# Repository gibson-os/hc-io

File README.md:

### Commands
| Number | Description           |
|--------|-----------------------|
| 128    | Set ports             |
| 129    | Add direct connect    |
| 130    | Set direct connect    |
| 131    | Delete direct connect |
| 132    | Reset direct connect  |
| 133    | Get direct connect    |
| 134    | Defrag direct connect |
| 135    | Status in EEPROM      |
| 136    | Direct connect status |

Basic commands: [Module readme](src/hc-module/README.md)

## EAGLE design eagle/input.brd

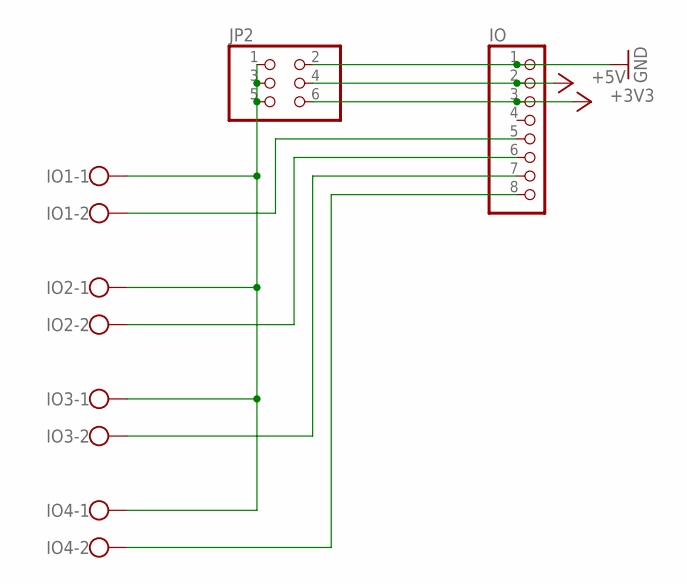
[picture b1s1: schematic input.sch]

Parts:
IO: PINHD-1X8; 1X08
IO1, IO2, IO3, IO4: W237-102
JP2: PINHD-2X3; 2X03

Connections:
+3V3: IO.3, JP2.6
+5V: IO.2, JP2.4
GND: IO.1, JP2.2
IO1: IO.5, IO1.2
IO2: IO.6, IO2.2
IO3: IO.7, IO3.2
IO4: IO.8, IO4.2
unnamed: IO1.1, IO2.1, IO3.1, IO4.1, JP2.1, JP2.3, JP2.5

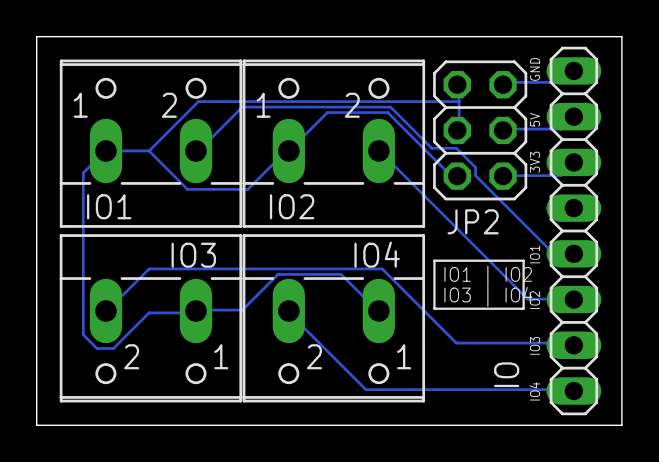
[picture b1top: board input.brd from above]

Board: 2 copper layers, 32.5 x 21.6 mm, 6 parts (0 on the bottom side), 8 nets.

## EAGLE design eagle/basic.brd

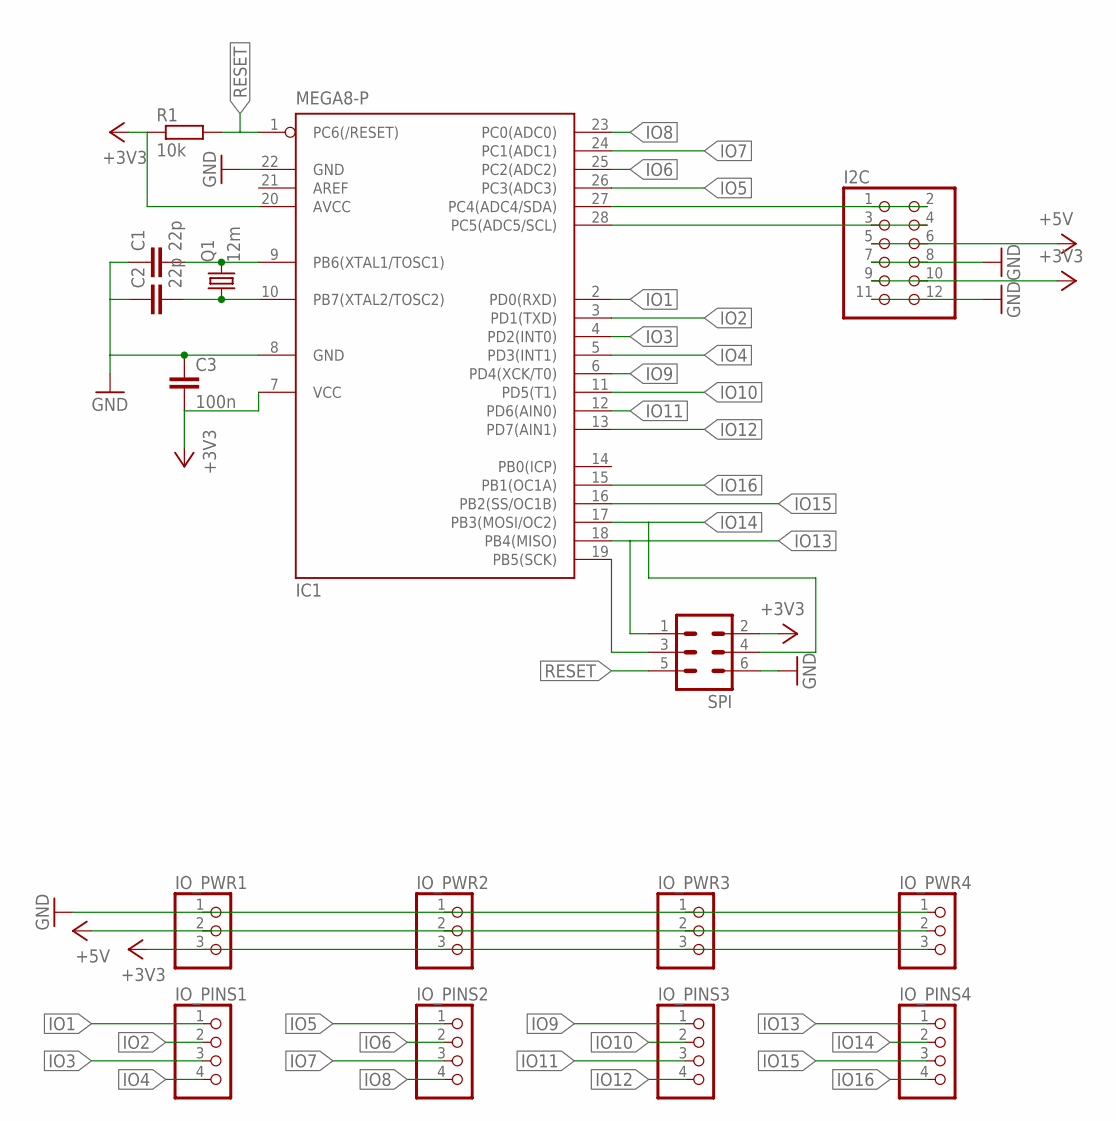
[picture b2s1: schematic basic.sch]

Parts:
C1, C2: 22p; C025-025X050
C3: 100n; C025-025X050
I2C: PINHD-2X6; 2X06
IC1: MEGA8-P; DIL28-3
IO_PINS1, IO_PINS2, IO_PINS3, IO_PINS4: PINHD-1X4; 1X04
IO_PWR1, IO_PWR2, IO_PWR3, IO_PWR4: PINHD-1X3; 1X03
Q1: 12m; HC49/S
R1: 10k; 0207/10
SPI: ML6

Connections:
+3V3: C3.2, I2C.9, I2C.10, IC1.7 (VCC), IC1.20 (AVCC), IO_PWR1.3, IO_PWR2.3, IO_PWR3.3, IO_PWR4.3, R1.1, SPI.2
+5V: I2C.5, I2C.6, IO_PWR1.2, IO_PWR2.2, IO_PWR3.2, IO_PWR4.2
GND: C1.1, C2.1, C3.1, I2C.7, I2C.8, I2C.11, I2C.12, IC1.8 (GND), IC1.22 (GND), IO_PWR1.1, IO_PWR2.1, IO_PWR3.1, IO_PWR4.1, SPI.6
IO1: IC1.2 (PD0(RXD)), IO_PINS1.1
IO2: IC1.3 (PD1(TXD)), IO_PINS1.2
IO3: IC1.4 (PD2(INT0)), IO_PINS1.3
IO4: IC1.5 (PD3(INT1)), IO_PINS1.4
IO5: IC1.26 (PC3(ADC3)), IO_PINS2.1
IO6: IC1.25 (PC2(ADC2)), IO_PINS2.2
IO7: IC1.24 (PC1(ADC1)), IO_PINS2.3
IO8: IC1.23 (PC0(ADC0)), IO_PINS2.4
IO9: IC1.6 (PD4(XCK/T0)), IO_PINS3.1
IO10: IC1.11 (PD5(T1)), IO_PINS3.2
IO11: IC1.12 (PD6(AIN0)), IO_PINS3.3
IO12: IC1.13 (PD7(AIN1)), IO_PINS3.4
IO13: IC1.18 (PB4(MISO)), IO_PINS4.1, SPI.1
IO14: IC1.17 (PB3(MOSI/OC2)), IO_PINS4.2, SPI.4
IO15: IC1.16 (PB2(SS/OC1B)), IO_PINS4.3
IO16: IC1.15 (PB1(OC1A)), IO_PINS4.4
unnamed: C2.2, IC1.10 (PB7(XTAL2/TOSC2)), Q1.1
unnamed: C1.2, IC1.9 (PB6(XTAL1/TOSC1)), Q1.2
unnamed: I2C.1, I2C.2, IC1.27 (PC4(ADC4/SDA))
unnamed: IC1.19 (PB5(SCK)), SPI.3
unnamed: I2C.3, I2C.4, IC1.28 (PC5(ADC5/SCL))
RESET: IC1.1 (PC6(/RESET)), R1.2, SPI.5

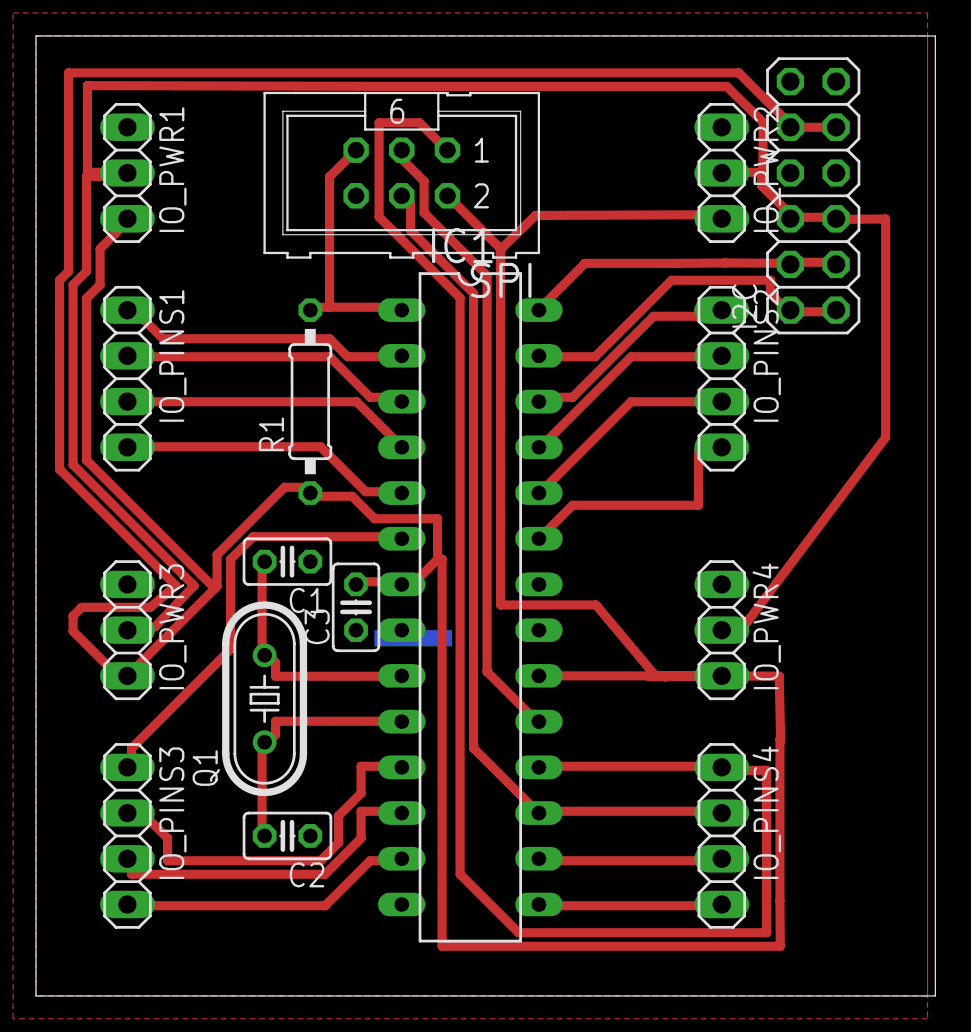
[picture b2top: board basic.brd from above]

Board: 2 copper layers, 50.0 x 53.3 mm, 16 parts (0 on the bottom side), 25 nets.

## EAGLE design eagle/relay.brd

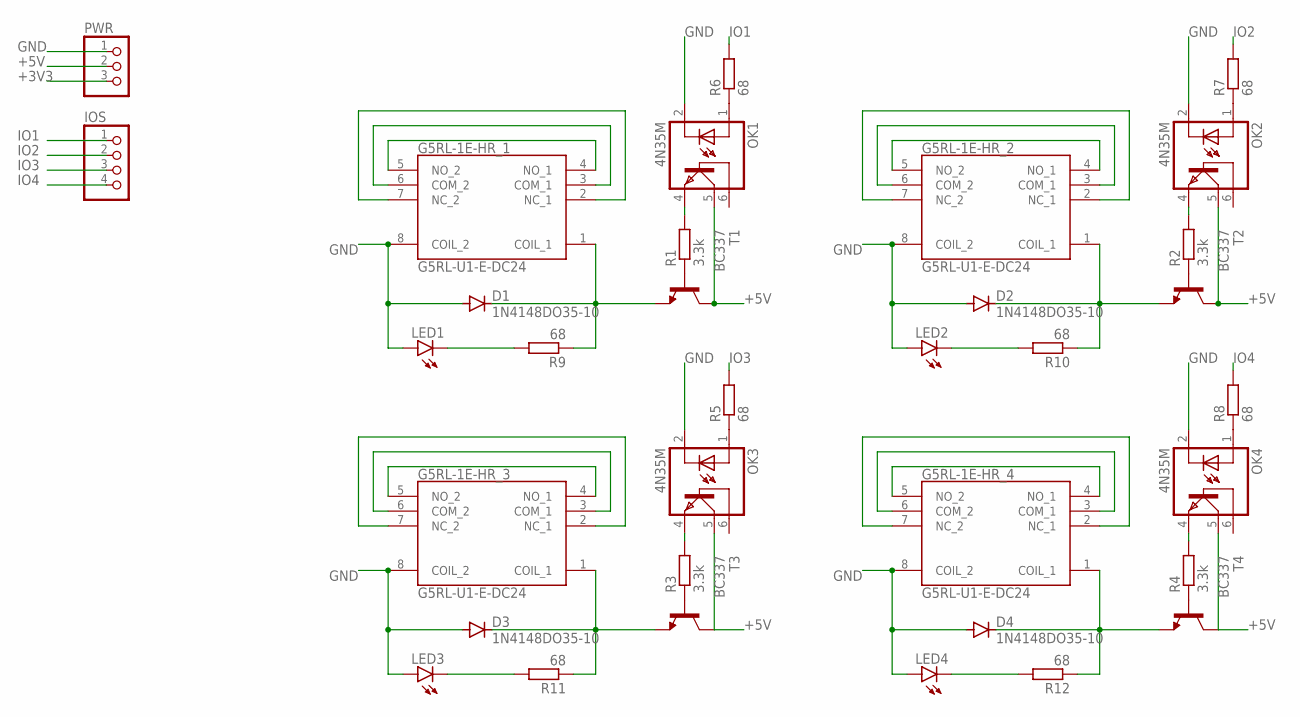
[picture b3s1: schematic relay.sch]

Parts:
D1, D2, D3, D4: 1N4148DO35-10; DO35-10
G5RL-1E-HR_1, G5RL-1E-HR_2, G5RL-1E-HR_3, G5RL-1E-HR_4: G5RL-U1-E-DC24; G5RLU1EDC24
IOS: PINHD-1X4; 1X04
LED1, LED2, LED3, LED4: LED3MM
OK1, OK2, OK3, OK4: 4N35M; DIL06
PWR: PINHD-1X3; 1X03
R1, R2, R3, R4: 3.3k; 0207/7
R5, R6, R7, R8, R9, R10, R11, R12: 68; 0204/7
T1, T2, T3, T4: BC337; TO92@1

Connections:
+3V3: PWR.3
+5V: OK1.5 (COL), OK2.5 (COL), OK3.5 (COL), OK4.5 (COL), PWR.2, T1.3 (C), T2.3 (C), T3.3 (C), T4.3 (C)
GND: D1.A, D2.A, D3.A, D4.A, G5RL-1E-HR_1.8 (COIL_2), G5RL-1E-HR_2.8 (COIL_2), G5RL-1E-HR_3.8 (COIL_2), G5RL-1E-HR_4.8 (COIL_2), LED1.A, LED2.A, LED3.A, LED4.A, OK1.2 (C), OK2.2 (C), OK3.2 (C), OK4.2 (C), PWR.1
IO1: IOS.1, R6.2
IO2: IOS.2, R7.2
IO3: IOS.3, R5.2
IO4: IOS.4, R8.2
unnamed: G5RL-1E-HR_1.4 (NO_1), G5RL-1E-HR_1.5 (NO_2)
unnamed: G5RL-1E-HR_1.3 (COM_1), G5RL-1E-HR_1.6 (COM_2)
unnamed: G5RL-1E-HR_1.2 (NC_1), G5RL-1E-HR_1.7 (NC_2)
unnamed: OK1.4 (EMI), R1.2
unnamed: D1.C, G5RL-1E-HR_1.1 (COIL_1), R9.1, T1.1 (E)
unnamed: R1.1, T1.2 (B)
unnamed: G5RL-1E-HR_2.4 (NO_1), G5RL-1E-HR_2.5 (NO_2)
unnamed: G5RL-1E-HR_2.3 (COM_1), G5RL-1E-HR_2.6 (COM_2)
unnamed: G5RL-1E-HR_2.2 (NC_1), G5RL-1E-HR_2.7 (NC_2)
unnamed: OK1.1 (A), R6.1
unnamed: D2.C, G5RL-1E-HR_2.1 (COIL_1), R10.1, T2.1 (E)
unnamed: R2.1, T2.2 (B)
unnamed: G5RL-1E-HR_3.4 (NO_1), G5RL-1E-HR_3.5 (NO_2)
unnamed: G5RL-1E-HR_3.3 (COM_1), G5RL-1E-HR_3.6 (COM_2)
unnamed: G5RL-1E-HR_3.2 (NC_1), G5RL-1E-HR_3.7 (NC_2)
unnamed: OK3.4 (EMI), R3.2
unnamed: D3.C, G5RL-1E-HR_3.1 (COIL_1), R11.1, T3.1 (E)
unnamed: R3.1, T3.2 (B)
unnamed: G5RL-1E-HR_4.4 (NO_1), G5RL-1E-HR_4.5 (NO_2)
unnamed: G5RL-1E-HR_4.3 (COM_1), G5RL-1E-HR_4.6 (COM_2)
unnamed: G5RL-1E-HR_4.2 (NC_1), G5RL-1E-HR_4.7 (NC_2)
unnamed: OK3.1 (A), R5.1
unnamed: D4.C, G5RL-1E-HR_4.1 (COIL_1), R12.1, T4.1 (E)
unnamed: R4.1, T4.2 (B)
unnamed: OK4.4 (EMI), R4.2
unnamed: OK2.4 (EMI), R2.2
unnamed: OK2.1 (A), R7.1
unnamed: OK4.1 (A), R8.1
unnamed: LED1.K (C), R9.2
unnamed: LED3.K (C), R11.2
unnamed: LED2.K (C), R10.2
unnamed: LED4.K (C), R12.2

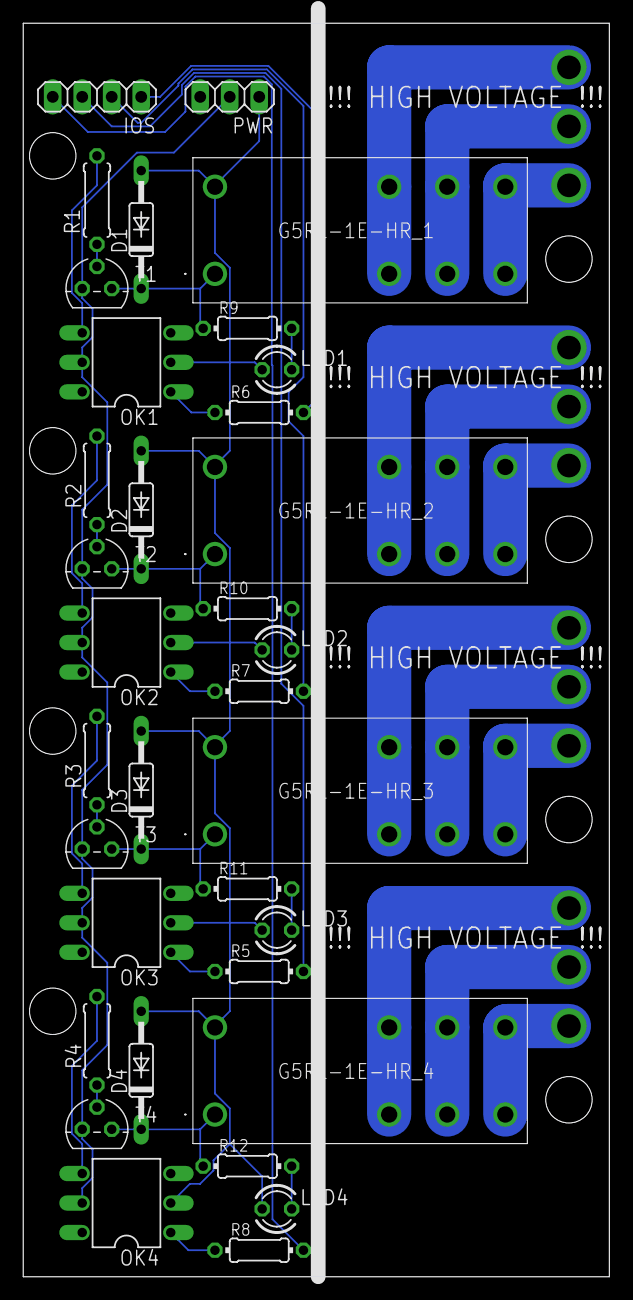
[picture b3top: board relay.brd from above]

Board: 2 copper layers, 50.5 x 107.9 mm, 34 parts (0 on the bottom side), 38 nets.

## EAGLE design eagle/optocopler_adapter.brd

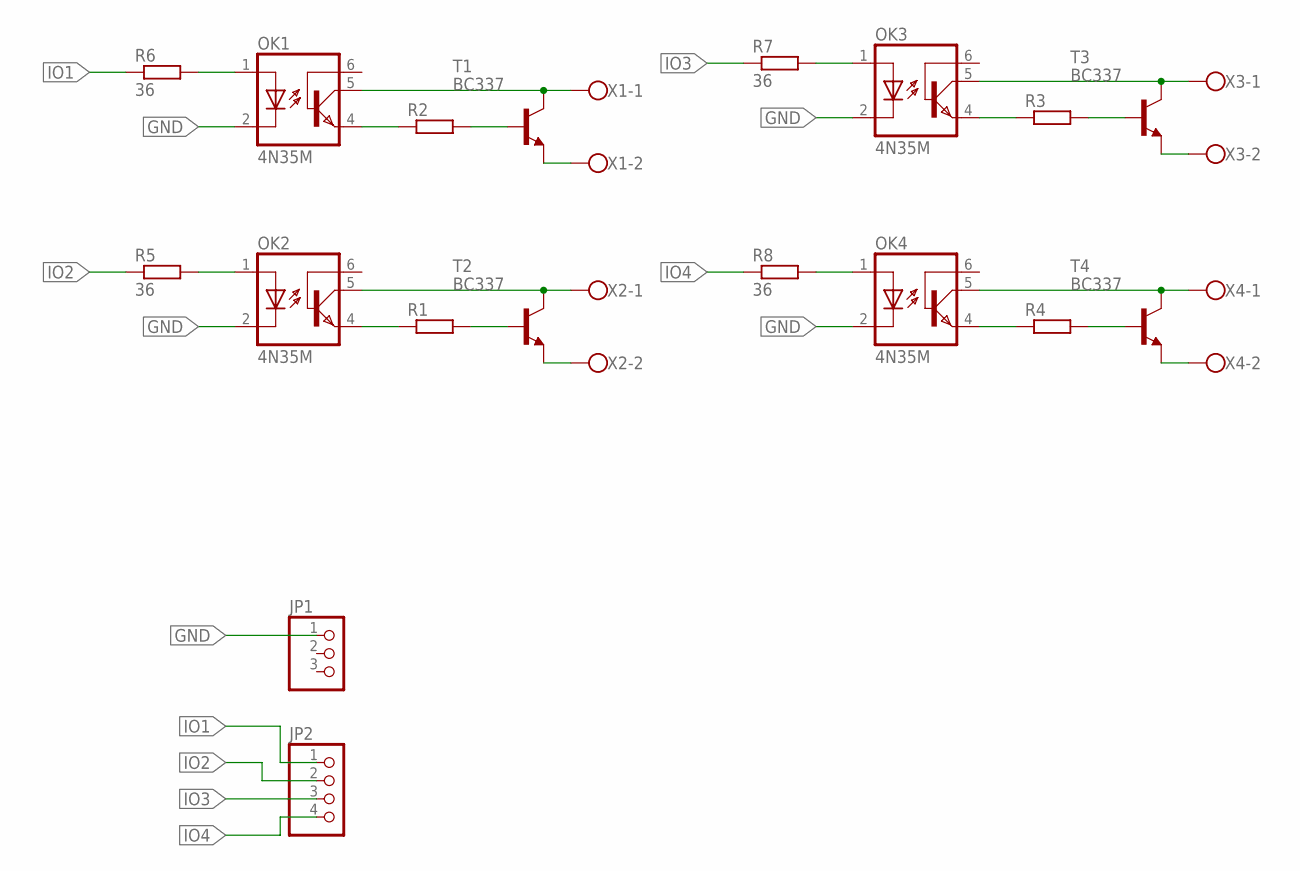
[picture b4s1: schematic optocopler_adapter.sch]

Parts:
JP1: PINHD-1X3/90; 1X03/90
JP2: PINHD-1X4/90; 1X04/90
OK1, OK2, OK3, OK4: 4N35M; DIL06
R1, R2, R3, R4: R-EU_0204/7; 0204/7
R5, R6, R7, R8: 36; 0204/7
T1, T2, T3, T4: BC337; TO92
X1, X2, X3, X4: W237-102

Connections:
GND: JP1.1, OK1.2 (C), OK2.2 (C), OK3.2 (C), OK4.2 (C)
IO1: JP2.1, R6.1
IO2: JP2.2, R5.1
IO3: JP2.3, R7.1
IO4: JP2.4, R8.1
unnamed: OK1.1 (A), R6.2
unnamed: OK1.4 (EMI), R2.1
unnamed: R2.2, T1.2 (B)
unnamed: OK1.5 (COL), T1.3 (C), X1.1
unnamed: T1.1 (E), X1.2
unnamed: OK2.1 (A), R5.2
unnamed: OK2.4 (EMI), R1.1
unnamed: R1.2, T2.2 (B)
unnamed: OK2.5 (COL), T2.3 (C), X2.1
unnamed: T2.1 (E), X2.2
unnamed: OK3.1 (A), R7.2
unnamed: OK3.4 (EMI), R3.1
unnamed: R3.2, T3.2 (B)
unnamed: OK3.5 (COL), T3.3 (C), X3.1
unnamed: T3.1 (E), X3.2
unnamed: OK4.1 (A), R8.2
unnamed: OK4.4 (EMI), R4.1
unnamed: R4.2, T4.2 (B)
unnamed: OK4.5 (COL), T4.3 (C), X4.1
unnamed: T4.1 (E), X4.2

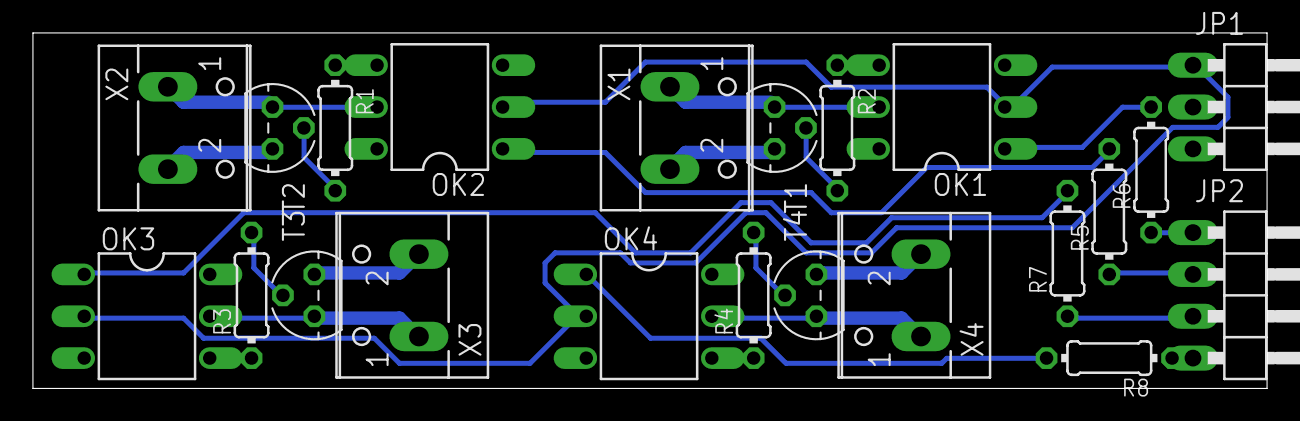
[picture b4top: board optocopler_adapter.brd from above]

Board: 2 copper layers, 74.9 x 21.6 mm, 22 parts (0 on the bottom side), 25 nets.

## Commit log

2022-12-18 Init commit
2022-12-18 Fix load module
2022-12-18 Add commands to readme
2022-12-18 Fix microchip studio project
2022-12-18 Remove ignored files
